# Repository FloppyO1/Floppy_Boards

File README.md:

# Floppy_Boards
Floppy Boards are a series of breakout boards for rapid prototyping which I developed as an alternative of Arduino.

These boards can provide good performance and many useful modules (such as: USB, I2C, SPI, timers etc.). I want to make several models, in order to have different boards for different applications.
For example, I am considering developing options for:

- Built-in battery monitoring & charging.   (to be done)
- Built-in DC motor control.                (to be done)
- Built-in servos & stepper-motor control.  (to be done)

# Why as an alternative to Arduino boards?
I am building this board because I was looking for a cheap, powerful and well supported development board in the marketplace, but I don’t find anything I like. On the other hand, I am learning a lot while making these Floppy Boards.
## Features
- Programmable with Arduino IDE and STMCubeIDE
- Planty of the module
- Small dimensions
- Lots of GPIO

### The most recent version I've made

The third version of the Floppy Board, this board has incorporated all possible improvements regarding the interface between the Floppy Board and the computer.
In this version, it excels over the others in the following aspects:

- The last upgrade includes a USB-C port, allowing you to power our projects and load firmware directly without the need for an ST-Link.
- Additionally, the board has been further downsized, featuring two holes on each side when inserted into a breadboard!
- I've added a pin where you can access the incoming 5V voltage from the USB , enabling you to power external circuits directly from the convenient USB-C.
- The silkscreen has been completely updated, making it much more legible and aesthetically pleasing.
- inally, we've introduced the option to install an EEPROM on the back of the board , enabling you to permanently save small amounts of data even in the absence of power.

## License

[CERN Open Hardware Licence Version 2 - Strongly Reciprocal](https://choosealicense.com/licenses/cern-ohl-s-2.0/#)

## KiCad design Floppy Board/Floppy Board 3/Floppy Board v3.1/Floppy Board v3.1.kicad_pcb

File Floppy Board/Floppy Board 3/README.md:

# Floppy Board rev:3.0/3.1

The third version of the Floppy Board, this board has incorporated all possible improvements regarding the interface between the Floppy Board and the computer.
In this version, it excels over the others in the following aspects:

- The last upgrade includes a USB-C port, allowing you to power our projects and load firmware directly without the need for an ST-Link.
- Additionally, the board has been further downsized, featuring two holes on each side when inserted into a breadboard!
- I've added a pin where you can access the incoming 5V voltage from the USB , enabling you to power external circuits directly from the convenient USB-C.
- The silkscreen has been completely updated, making it much more legible and aesthetically pleasing.
- inally, we've introduced the option to install an EEPROM on the back of the board , enabling you to permanently save small amounts of data even in the absence of power.

## License

[CERN Open Hardware Licence Version 2 - Strongly Reciprocal](https://choosealicense.com/licenses/cern-ohl-s-2.0/#)

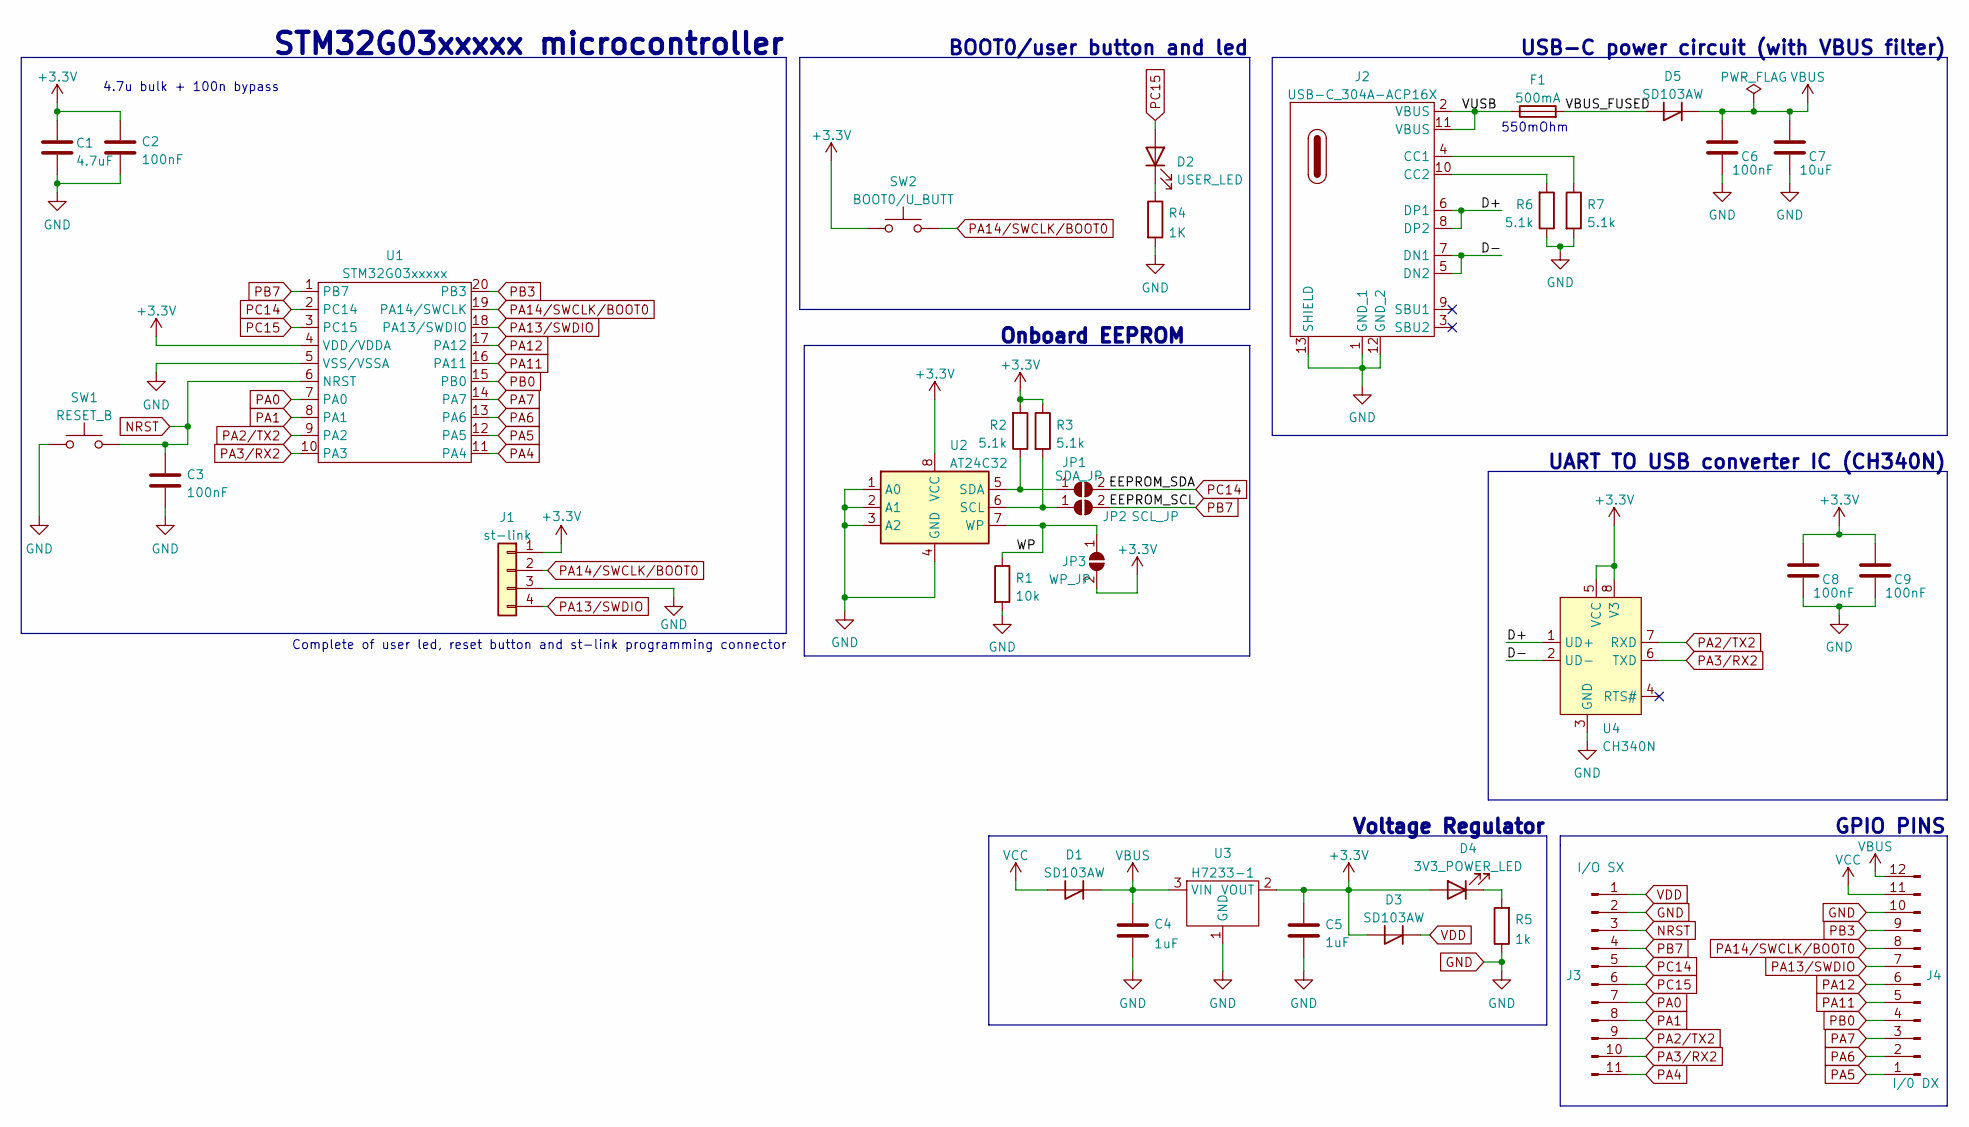
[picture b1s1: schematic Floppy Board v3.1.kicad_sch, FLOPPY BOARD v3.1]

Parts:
C1: 4.7uF; C_0805_2012Metric_Pad1.18x1.45mm_HandSolder
C2, C3, C6, C8, C9: 100nF; C_0805_2012Metric_Pad1.18x1.45mm_HandSolder
C4, C5: 1uF; C_0805_2012Metric_Pad1.18x1.45mm_HandSolder
C7: 10uF; C_0805_2012Metric_Pad1.18x1.45mm_HandSolder
D1, D5: SD103AW; D_SOD-123
D2: USER_LED; LED_0805_2012Metric_Pad1.15x1.40mm_HandSolder
D3: SD103AW; D_SOD-123F
D4: 3V3_POWER_LED; LED_0805_2012Metric_Pad1.15x1.40mm_HandSolder
F1: 500mA; Fuse_1206_3216Metric_Pad1.42x1.75mm_HandSolder
J1: st-link; PinHeader_1x04_P2.54mm_Vertical
J2: USB-C_304A-ACP16X; USB_C_304A-ACP16X
J3: I/O SX; PinHeader_1x11_P2.54mm_Vertical
J4: I/0 DX; PinHeader_1x12_P2.54mm_Vertical
JP1: SDA_JP; SolderJumper-2_P1.3mm_Open_RoundedPad1.0x1.5mm
JP2: SCL_JP; SolderJumper-2_P1.3mm_Open_RoundedPad1.0x1.5mm
JP3: WP_JP; SolderJumper-2_P1.3mm_Open_RoundedPad1.0x1.5mm
R1: 10k; R_0805_2012Metric_Pad1.20x1.40mm_HandSolder
R2, R3, R6, R7: 5.1k; R_0805_2012Metric_Pad1.20x1.40mm_HandSolder
R4: 1K; R_0805_2012Metric_Pad1.20x1.40mm_HandSolder
R5: 1k; R_0805_2012Metric_Pad1.20x1.40mm_HandSolder
SW1: RESET_B; SMD BUTTON 5.1x5.1
SW2: BOOT0/U_BUTT; SMD BUTTON 5.1x5.1
U1: STM32G03xxxxx; TSSOP-20_4.4x6.5mm_P0.65mm
U2: AT24C32; SOP-8_3.9x4.9mm_P1.27mm
U3: H7233-1; SOT-23
U4: CH340N; SOP-8_3.9x4.9mm_P1.27mm

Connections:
+3V3: C1.1, C2.1, C5.1, C8.1, C9.1, D3.2 (A), D4.2 (A), J1.1, JP3.2 (B), R2.2, R3.1, SW2.1, U1.4 (VDD/VDDA), U2.8 (VCC), U3.2 (VOUT), U4.5 (VCC), U4.8 (V3)
/D+: J2.6 (DP1), J2.8 (DP2), U4.1 (UD+)
/D-: J2.5 (DN2), J2.7 (DN1), U4.2 (UD-)
/VBUS_FUSED: D5.2 (A), F1.2
/VUSB: F1.1, J2.2 (VBUS), J2.11 (VBUS)
/WP: JP3.1 (A), R1.1, U2.7 (WP)
GND: C1.2, C2.2, C3.2, C4.2, C5.2, C6.2, C7.2, C8.2, C9.2, J1.3, J2.1 (GND_1), J2.12 (GND_2), J2.13 (SHIELD), J3.2, J4.10, R1.2, R4.2, R5.1, R6.1, R7.2, SW1.1, U1.5 (VSS/VSSA), U2.1 (A0), U2.2 (A1), U2.3 (A2), U2.4 (GND), U3.1 (GND), U4.3 (GND)
NRST: C3.1, J3.3, SW1.2, U1.6 (NRST)
unnamed: D2.1 (K), R4.1
unnamed: D4.1 (K), R5.2
unnamed: J2.4 (CC1), R7.1
unnamed: J2.10 (CC2), R6.2
unnamed: JP1.1 (A), R2.1, U2.5 (SDA)
unnamed: JP2.1 (A), R3.2, U2.6 (SCL)
PA0: J3.7, U1.7 (PA0)
PA1: J3.8, U1.8 (PA1)
PA2/TX2: J3.9, U1.9 (PA2), U4.7 (RXD)
PA3/RX2: J3.10, U1.10 (PA3), U4.6 (TXD)
PA4: J3.11, U1.11 (PA4)
PA5: J4.1, U1.12 (PA5)
PA6: J4.2, U1.13 (PA6)
PA7: J4.3, U1.14 (PA7)
PA11: J4.5, U1.16 (PA11)
PA12: J4.6, U1.17 (PA12)
PA13/SWDIO: J1.4, J4.7, U1.18 (PA13/SWDIO)
PA14/SWCLK/BOOT0: J1.2, J4.8, SW2.2, U1.19 (PA14/SWCLK)
PB0: J4.4, U1.15 (PB0)
PB3: J4.9, U1.20 (PB3)
PB7: J3.4, JP2.2 (B), U1.1 (PB7)
PC14: J3.5, JP1.2 (B), U1.2 (PC14)
PC15: D2.2 (A), J3.6, U1.3 (PC15)
VBUS: C4.1, C6.1, C7.1, D1.1 (K), D5.1 (K), J4.12, U3.3 (VIN)
VCC: D1.2 (A), J4.11
VDD: D3.1 (K), J3.1

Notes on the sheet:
USB-C power circuit (with VBUS filter)
4.7u bulk + 100n bypass
Voltage Regulator
STM32G03xxxxx microcontroller
550mOhm
GPIO PINS
UART TO USB converter IC (CH340N)
BOOT0/user button and led
Complete of user led, reset button and st-link programming connector
Onboard EEPROM

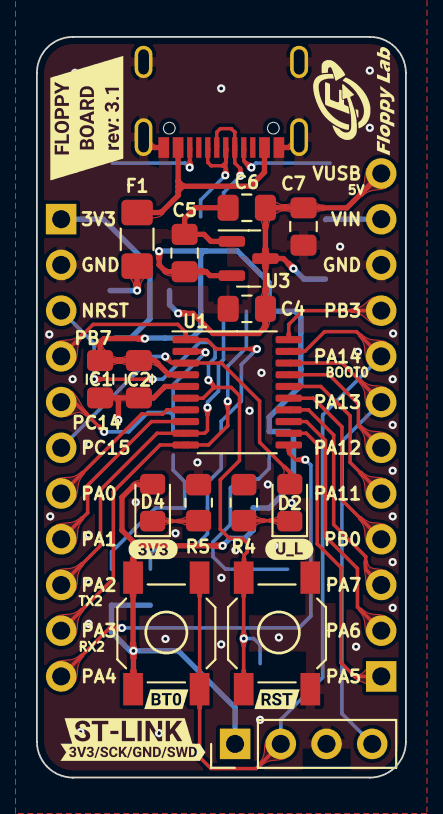
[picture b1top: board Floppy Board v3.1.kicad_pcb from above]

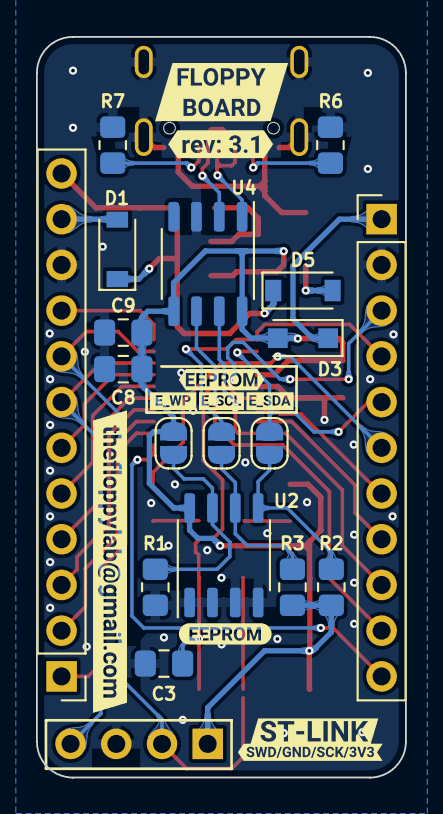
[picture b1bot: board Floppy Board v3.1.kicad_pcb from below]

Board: 2 copper layers, 20.5 x 41.1 mm, 52 parts (28 on the bottom side), 34 nets.

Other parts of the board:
kibuzzard-644D5A83: G***; kibuzzard-644D5A83
kibuzzard-644D5AD1: G***; kibuzzard-644D5AD1
kibuzzard-644D5AFD: G***; kibuzzard-644D5AFD
kibuzzard-644D5B14: G***; kibuzzard-644D5B14
kibuzzard-644D5C5F: G***; kibuzzard-644D5C5F
kibuzzard-644D5C68: G***; kibuzzard-644D5C68
kibuzzard-644D5C93: G***; kibuzzard-644D5C93
kibuzzard-644D5CBA: G***; kibuzzard-644D5CBA
kibuzzard-644D5F43: G***; kibuzzard-644D5F43
kibuzzard-644D56F9: G***; kibuzzard-644D56F9
kibuzzard-644D58F1: G***; kibuzzard-644D58F1
kibuzzard-644D571B: G***; kibuzzard-644D571B
kibuzzard-644D5750: G***; kibuzzard-644D5750
kibuzzard-644D5758: G***; kibuzzard-644D5758
kibuzzard-644D5814: G***; kibuzzard-644D5814
kibuzzard-644D5953: G***; kibuzzard-644D5953
kibuzzard-644D6722: G***; kibuzzard-644D6722

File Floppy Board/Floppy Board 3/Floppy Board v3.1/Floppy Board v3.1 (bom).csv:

"Reference","Value","Footprint","Qtà"
"C1","4.7uF","Capacitor_SMD:C_0805_2012Metric_Pad1.18x1.45mm_HandSolder","1"
"C2, C3, C6, C8, C9","100nF","Capacitor_SMD:C_0805_2012Metric_Pad1.18x1.45mm_HandSolder","5"
"C4, C5","1uF","Capacitor_SMD:C_0805_2012Metric_Pad1.18x1.45mm_HandSolder","2"
"C7","10uF","Capacitor_SMD:C_0805_2012Metric_Pad1.18x1.45mm_HandSolder","1"
"D1, D5","SD103AW","Diode_SMD:D_SOD-123","2"
"D2","USER_LED","LED_SMD:LED_0805_2012Metric_Pad1.15x1.40mm_HandSolder","1"
"D3","SD103AW","Diode_SMD:D_SOD-123F","1"
"D4","3V3_POWER_LED","LED_SMD:LED_0805_2012Metric_Pad1.15x1.40mm_HandSolder","1"
"F1","500mA","Fuse:Fuse_1206_3216Metric_Pad1.42x1.75mm_HandSolder","1"
"J1","st-link","Connector_PinHeader_2.54mm:PinHeader_1x04_P2.54mm_Vertical","1"
"J2","USB-C_304A-ACP16X","_MIA footprint:USB_C_304A-ACP16X","1"
"J3","I/O SX","Connector_PinHeader_2.54mm:PinHeader_1x11_P2.54mm_Vertical","1"
"J4","I/0 DX","Connector_PinHeader_2.54mm:PinHeader_1x12_P2.54mm_Vertical","1"
"JP1","SDA_JP","Jumper:SolderJumper-2_P1.3mm_Open_RoundedPad1.0x1.5mm","1"
"JP2","SCL_JP","Jumper:SolderJumper-2_P1.3mm_Open_RoundedPad1.0x1.5mm","1"
"JP3","WP_JP","Jumper:SolderJumper-2_P1.3mm_Open_RoundedPad1.0x1.5mm","1"
"R1","10k","Resistor_SMD:R_0805_2012Metric_Pad1.20x1.40mm_HandSolder","1"
"R2, R3, R6, R7","5.1k","Resistor_SMD:R_0805_2012Metric_Pad1.20x1.40mm_HandSolder","4"
"R4","1K","Resistor_SMD:R_0805_2012Metric_Pad1.20x1.40mm_HandSolder","1"
"R5","1k","Resistor_SMD:R_0805_2012Metric_Pad1.20x1.40mm_HandSolder","1"
"SW1","RESET_B","_MIA footprint:SMD BUTTON 5.1x5.1","1"
"SW2","BOOT0/U_BUTT","_MIA footprint:SMD BUTTON 5.1x5.1","1"
"U1","STM32G03xxxxx","Package_SO:TSSOP-20_4.4x6.5mm_P0.65mm","1"
"U2","AT24C32","Package_SO:SOP-8_3.9x4.9mm_P1.27mm","1"
"U3","H7233-1","Package_TO_SOT_SMD:SOT-23","1"
"U4","CH340N","Package_SO:SOP-8_3.9x4.9mm_P1.27mm","1"

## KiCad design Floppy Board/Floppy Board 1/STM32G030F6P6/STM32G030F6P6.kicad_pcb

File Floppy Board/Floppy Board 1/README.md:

# Floppy Board rev:1.0

This is the first prototype of the Floppy Board.

## License

[CERN Open Hardware Licence Version 2 - Strongly Reciprocal](https://choosealicense.com/licenses/cern-ohl-s-2.0/#)

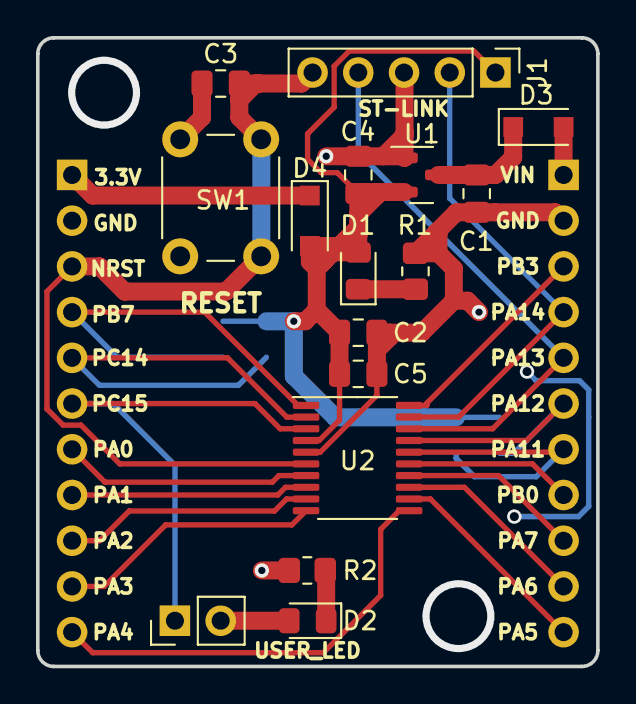
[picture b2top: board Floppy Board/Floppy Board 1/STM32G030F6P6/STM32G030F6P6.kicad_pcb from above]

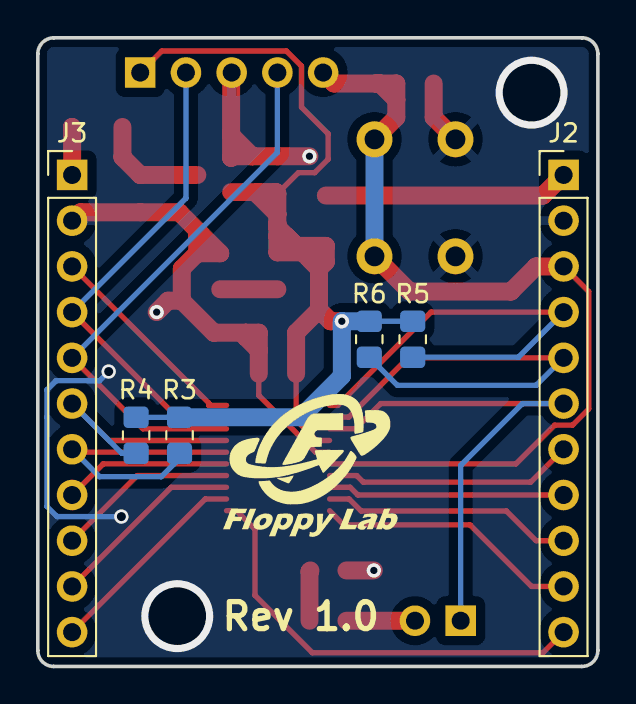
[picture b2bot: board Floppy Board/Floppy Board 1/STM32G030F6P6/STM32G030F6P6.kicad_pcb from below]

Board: 2 copper layers, 31.1 x 34.9 mm, 22 parts (6 on the bottom side), 26 nets.

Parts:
C1, C4: 1u; C_0805_2012Metric_Pad1.18x1.45mm_HandSolder
C2: 4.7u; C_0805_2012Metric_Pad1.18x1.45mm_HandSolder
C3: 0.1U; C_0805_2012Metric_Pad1.18x1.45mm_HandSolder
C5: 100n; C_0805_2012Metric_Pad1.18x1.45mm_HandSolder
D1: POWER_LED; LED_0805_2012Metric_Pad1.15x1.40mm_HandSolder
D2: USER_LED; LED_0805_2012Metric_Pad1.15x1.40mm_HandSolder
D3, D4: 1N4002; D_SOD-123F
J1: stlink; PinHeader_1x05_P2.54mm_Vertical
J2: I/O SX; PinHeader_1x11_P2.54mm_Vertical
J3: I/0 DX; PinHeader_1x11_P2.54mm_Vertical
JP1: UL JUMP.; PinHeader_1x02_P2.54mm_Vertical
R1: 1k; R_0805_2012Metric_Pad1.20x1.40mm_HandSolder
R2: 1K; R_0805_2012Metric_Pad1.20x1.40mm_HandSolder
R3, R4, R5, R6: 4.7k; R_0805_2012Metric_Pad1.20x1.40mm_HandSolder
SW1: RESET_BUTTON; SW_PUSH_6mm
U1: H7233-1; SOT-23
U2: STM32G030F6P6; TSSOP-20_4.4x6.5mm_P0.65mm

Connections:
+3V3: C2.1, C4.1, C5.1, D1.2 (A), D4.2 (A), J1.1, R3.1, R4.1, R5.1, R6.1, U1.2 (VOUT), U2.4 (VDD/VDDA)
GND: C1.2, C2.2, C3.2, C4.2, C5.2, J1.3, J2.2, J3.2, R1.1, R2.2, SW1.1, U1.1 (GND), U2.5 (VSS/VSSA)
NRST: C3.1, J1.5, J2.3, SW1.2, U2.6 (NRST)
unnamed: C1.1, D3.1 (K), U1.3 (VIN)
unnamed: D1.1 (K), R1.2
unnamed: D2.1 (K), R2.1
unnamed: D2.2 (A), JP1.2 (B)
PA0: J2.7, U2.7 (PA0)
PA1: J2.8, U2.8 (PA1)
PA2: J2.9, U2.9 (PA2)
PA3: J2.10, U2.10 (PA3)
PA4: J2.11, U2.11 (PA4)
PA5: J3.11, U2.12 (PA5)
PA6: J3.10, U2.13 (PA6)
PA7: J3.9, U2.14 (PA7)
PA11: J3.7, R3.2, U2.16 (PA11)
PA12: J3.6, R4.2, U2.17 (PA12)
PA13/SWDIO: J1.4, J3.5, U2.18 (PA13/SWDIO)
PA14/SWCLK: J1.2, J3.4, U2.19 (PA14/SWCLK)
PB0: J3.8, U2.15 (PB0)
PB3: J3.3, U2.20 (PB3)
PB7: J2.4, R5.2, U2.1 (PB7)
PC14: J2.5, R6.2, U2.2 (PC14)
PC15: J2.6, JP1.1 (A), U2.3 (PC15)
VDD: D4.1 (K), J2.1
VIN: D3.2 (A), J3.1

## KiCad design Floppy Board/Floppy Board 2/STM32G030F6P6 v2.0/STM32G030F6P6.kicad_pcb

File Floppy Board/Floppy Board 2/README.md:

# Floppy Board rev:2.0

This is the second version of the Floppy Board, and it includes a few small improvements that make it simpler and faster to use.
The improvements that I made are as follows:

- The total width has been reduced, allowing this version to be used with only one breadboard.
- The 3.3V output pin now has precisely 3.3V (3.263V), ensuring no more 3V output!
- Pin names have been added on each side of the board.
- The board now has a slimmer profile that makes it possible to use it upside down.
- The microcontroller is the same as the first Floppy Board, but it can be upgraded with an equivalent MCU that has double the FLASH memory. The more capable MCU is the STM32G031F8P6, which has 32kB more memory than the old one (so 64kB in total). These boards are compatible with Arduino IDE, meaning they can be easily programmed by users who are less experienced.

## License

[CERN Open Hardware Licence Version 2 - Strongly Reciprocal](https://choosealicense.com/licenses/cern-ohl-s-2.0/#)

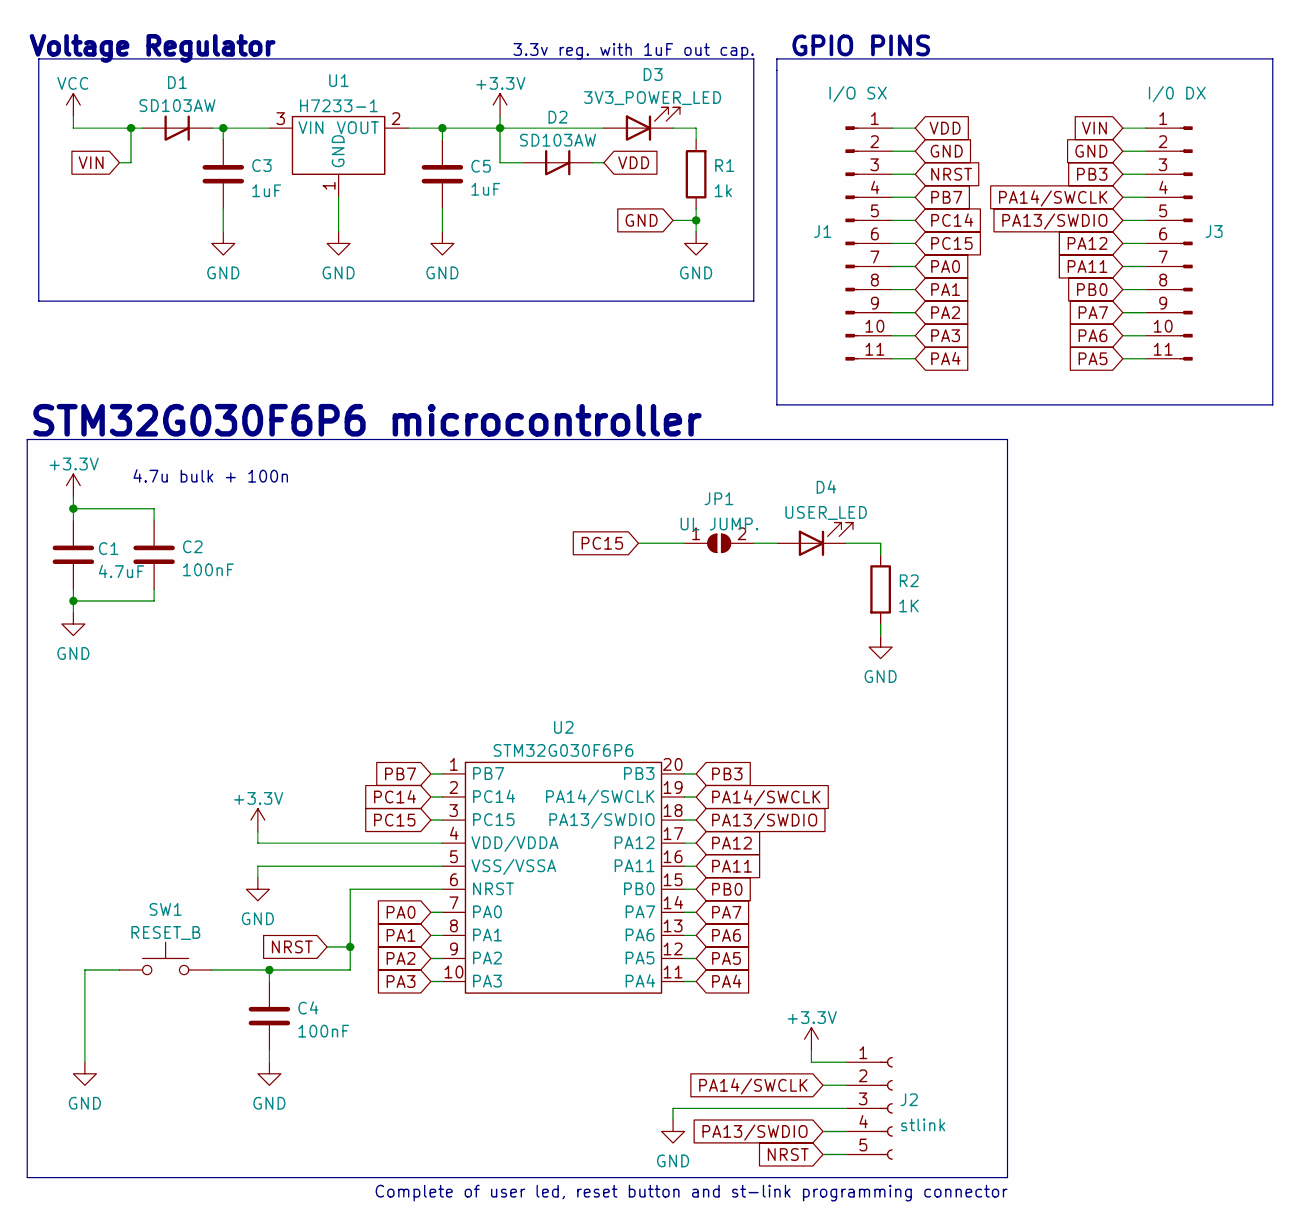
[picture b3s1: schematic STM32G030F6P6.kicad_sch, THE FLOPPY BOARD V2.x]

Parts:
C1: 4.7uF; C_0805_2012Metric_Pad1.18x1.45mm_HandSolder
C2, C4: 100nF; C_0805_2012Metric_Pad1.18x1.45mm_HandSolder
C3, C5: 1uF; C_0805_2012Metric_Pad1.18x1.45mm_HandSolder
D1: SD103AW; D_SOD-123
D2: SD103AW; D_SOD-123F
D3: 3V3_POWER_LED; LED_0805_2012Metric_Pad1.15x1.40mm_HandSolder
D4: USER_LED; LED_0805_2012Metric_Pad1.15x1.40mm_HandSolder
J1: I/O SX; PinHeader_1x11_P2.54mm_Vertical
J2: stlink; PinHeader_1x05_P2.54mm_Vertical
J3: I/0 DX; PinHeader_1x11_P2.54mm_Vertical
JP1: UL JUMP.; SolderJumper-2_P1.3mm_Open_RoundedPad1.0x1.5mm
R1: 1k; R_0805_2012Metric_Pad1.20x1.40mm_HandSolder
R2: 1K; R_0805_2012Metric_Pad1.20x1.40mm_HandSolder
SW1: RESET_B; SMD BUTTON 5.1x5.1
U1: H7233-1; SOT-23
U2: STM32G030F6P6; TSSOP-20_4.4x6.5mm_P0.65mm

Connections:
+3V3: C1.1, C2.1, C5.1, D2.2 (A), D3.2 (A), J2.1, U1.2 (VOUT), U2.4 (VDD/VDDA)
GND: C1.2, C2.2, C3.2, C4.2, C5.2, J1.2, J2.3, J3.2, R1.1, R2.2, SW1.1, U1.1 (GND), U2.5 (VSS/VSSA)
NRST: C4.1, J1.3, J2.5, SW1.2, U2.6 (NRST)
unnamed: C3.1, D1.1 (K), U1.3 (VIN)
unnamed: D3.1 (K), R1.2
unnamed: D4.1 (K), R2.1
unnamed: D4.2 (A), JP1.2 (B)
PA0: J1.7, U2.7 (PA0)
PA1: J1.8, U2.8 (PA1)
PA2: J1.9, U2.9 (PA2)
PA3: J1.10, U2.10 (PA3)
PA4: J1.11, U2.11 (PA4)
PA5: J3.11, U2.12 (PA5)
PA6: J3.10, U2.13 (PA6)
PA7: J3.9, U2.14 (PA7)
PA11: J3.7, U2.16 (PA11)
PA12: J3.6, U2.17 (PA12)
PA13/SWDIO: J2.4, J3.5, U2.18 (PA13/SWDIO)
PA14/SWCLK: J2.2, J3.4, U2.19 (PA14/SWCLK)
PB0: J3.8, U2.15 (PB0)
PB3: J3.3, U2.20 (PB3)
PB7: J1.4, U2.1 (PB7)
PC14: J1.5, U2.2 (PC14)
PC15: J1.6, JP1.1 (A), U2.3 (PC15)
VDD: D2.1 (K), J1.1
VIN: D1.2 (A), J3.1

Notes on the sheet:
3.3v reg. with 1uF out cap.
GPIO PINS
4.7u bulk + 100n
Complete of user led, reset button and st-link programming connector
STM32G030F6P6 microcontroller
Voltage Regulator

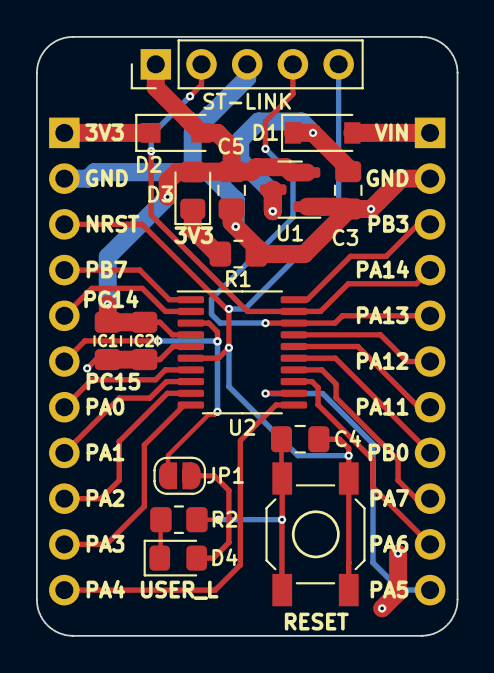
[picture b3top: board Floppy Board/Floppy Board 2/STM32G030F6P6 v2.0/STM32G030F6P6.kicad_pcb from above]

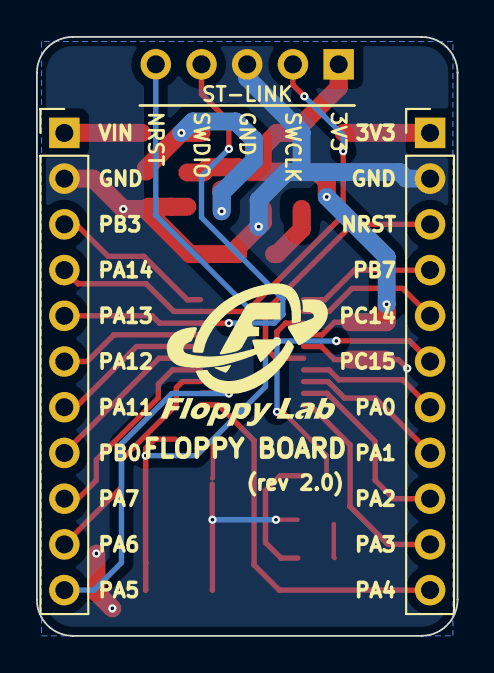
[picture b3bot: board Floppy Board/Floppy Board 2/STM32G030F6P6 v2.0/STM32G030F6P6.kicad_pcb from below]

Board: 2 copper layers, 23.4 x 33.3 mm, 18 parts (2 on the bottom side), 26 nets.

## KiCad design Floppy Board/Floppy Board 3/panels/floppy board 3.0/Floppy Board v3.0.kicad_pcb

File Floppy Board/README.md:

# Floppy Board

Inside this folder there are all the files of the base version of the Floppy Board.

There are 3 major versions:
- v1.0, that is the first prototype that I've made.
- v2.0, which is the second attempt, is an improved version of 1.0, it is good because it is the smallest of the three versions.
- v3.x, which is the last version that includes the connections between the Floppy Board and the computer.

## License

[CERN Open Hardware Licence Version 2 - Strongly Reciprocal](https://choosealicense.com/licenses/cern-ohl-s-2.0/#)

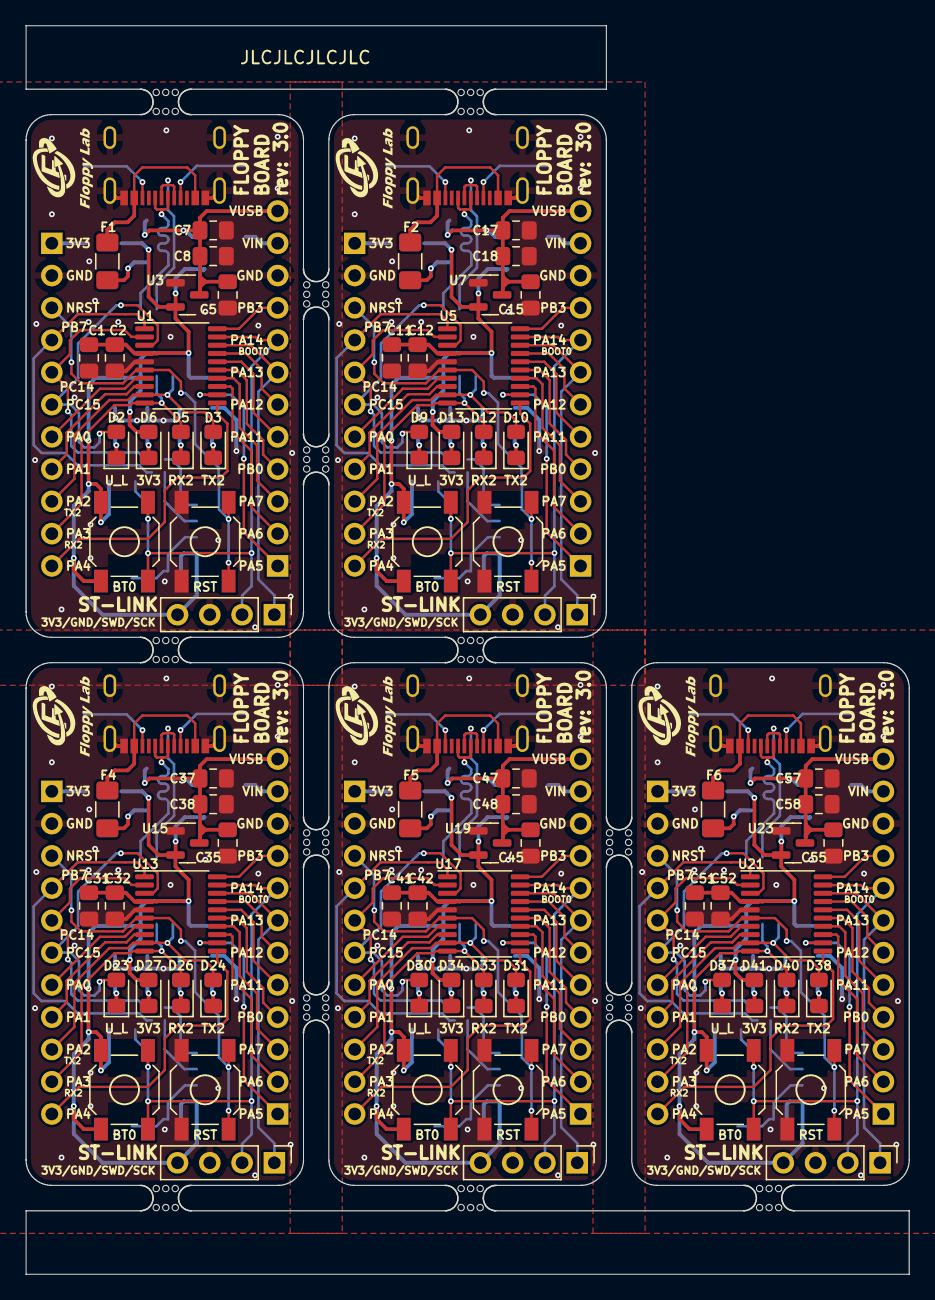
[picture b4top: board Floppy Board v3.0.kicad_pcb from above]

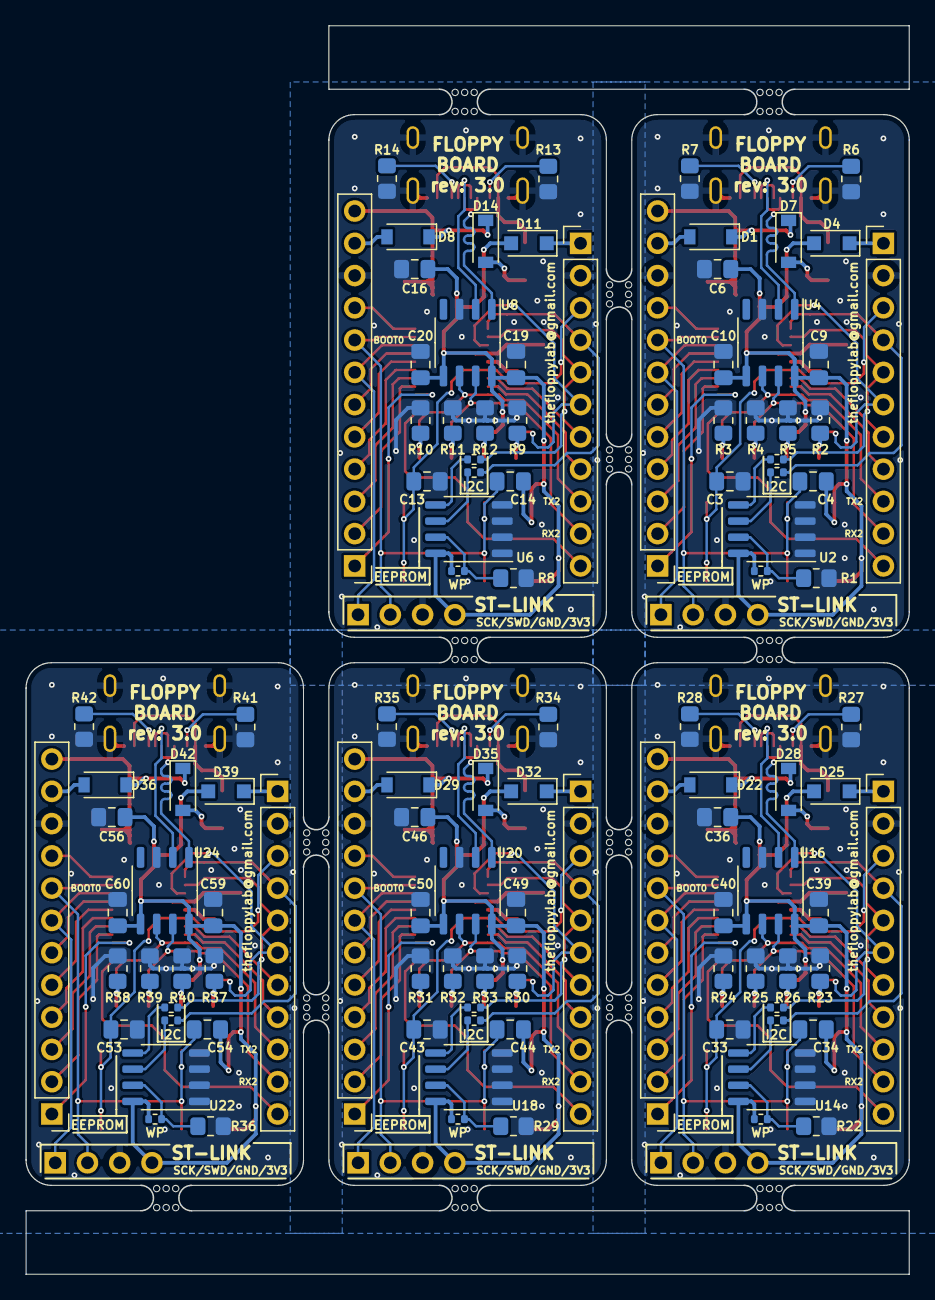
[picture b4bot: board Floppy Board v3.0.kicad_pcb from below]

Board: 2 copper layers, 69.5 x 98.3 mm, 203 parts (110 on the bottom side), 36 nets.

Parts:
C1, C11, C31, C41, C51: 4.7uF; C_0805_2012Metric_Pad1.18x1.45mm_HandSolder
C2, C3, C4, C7, C9, C10, C12, C13, C14, C17, C19, C20, C32, C33, C34, C37, C39, C40, C42, C43, C44, C47, C49, C50, C52, C53, C54, C57, C59, C60: 100nF; C_0805_2012Metric_Pad1.18x1.45mm_HandSolder
C5, C6, C15, C16, C35, C36, C45, C46, C55, C56: 1uF; C_0805_2012Metric_Pad1.18x1.45mm_HandSolder
C8, C18, C38, C48, C58: 10uF; C_0805_2012Metric_Pad1.18x1.45mm_HandSolder
D1, D7, D8, D14, D22, D28, D29, D35, D36, D42: SD103AW; D_SOD-123
D2, D9, D23, D30, D37: USER_LED; LED_0805_2012Metric_Pad1.15x1.40mm_HandSolder
D3, D10, D24, D31, D38: TX2; LED_0805_2012Metric_Pad1.15x1.40mm_HandSolder
D4, D11, D25, D32, D39: SD103AW; D_SOD-123F
D5, D12, D26, D33, D40: RX2; LED_0805_2012Metric_Pad1.15x1.40mm_HandSolder
D6, D13, D27, D34, D41: 3V3_POWER_LED; LED_0805_2012Metric_Pad1.15x1.40mm_HandSolder
F1, F2, F4, F5, F6: 500mA; Fuse_1206_3216Metric_Pad1.42x1.75mm_HandSolder
J1, J5, J13, J17, J21: st-link; PinHeader_1x04_P2.54mm_Vertical
J2, J6, J14, J18, J22: USB-C_304A-ACP16X; USB_C_304A-ACP16X
J3, J7, J15, J19, J23: I/O SX; PinHeader_1x11_P2.54mm_Vertical
J4, J8, J16, J20, J24: I/0 DX; PinHeader_1x12_P2.54mm_Vertical
JP1, JP4, JP10, JP13, JP16: SDA_JP; R_0402_1005Metric
JP2, JP5, JP11, JP14, JP17: SCL_JP; R_0402_1005Metric
JP3, JP6, JP12, JP15, JP18: WP_JP; R_0402_1005Metric
R1, R8, R22, R29, R36: 10k; R_0805_2012Metric_Pad1.20x1.40mm_HandSolder
R2, R3, R4, R9, R10, R11, R23, R24, R25, R30, R31, R32, R37, R38, R39: 1K; R_0805_2012Metric_Pad1.20x1.40mm_HandSolder
R5, R12, R26, R33, R40: 1k; R_0805_2012Metric_Pad1.20x1.40mm_HandSolder
R6, R7, R13, R14, R27, R28, R34, R35, R41, R42: 5.1k; R_0805_2012Metric_Pad1.20x1.40mm_HandSolder
SW1, SW3, SW7, SW9, SW11: RESET_B; SMD BUTTON 5.1x5.1
SW2, SW4, SW8, SW10, SW12: BOOT0/U_BUTT; SMD BUTTON 5.1x5.1
U1, U5, U13, U17, U21: STM32G03xxxxx; TSSOP-20_4.4x6.5mm_P0.65mm
U2, U6, U14, U18, U22: AT24C32; SOP-8_3.9x4.9mm_P1.27mm
U3, U7, U15, U19, U23: H7233-1; SOT-23
U4, U8, U16, U20, U24: CH340N; SOP-8_3.9x4.9mm_P1.27mm
mouse-bite-2mm-slot, mouse-bite-2mm-slot#2, mouse-bite-2mm-slot#3, mouse-bite-2mm-slot#4, mouse-bite-2mm-slot#5, mouse-bite-2mm-slot#6, mouse-bite-2mm-slot#7, mouse-bite-2mm-slot#8, mouse-bite-2mm-slot#9, mouse-bite-2mm-slot#10, mouse-bite-2mm-slot#11, mouse-bite-2mm-slot#12, mouse-bite-2mm-slot#13: VAL**; mouse-bite-2mm-slot

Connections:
+3V3: C1.1, C2.1, C4.2, C6.1, C9.1, C10.1, C11.1, C12.1, C14.2, C16.1, C19.1, C20.1, C31.1, C32.1, C34.2, C36.1, C39.1, C40.1, C41.1, C42.1, C44.2, C46.1, C49.1, C50.1, C51.1, C52.1, C54.2, C56.1, C59.1, C60.1, D4.2 (A), D6.2 (A), D11.2 (A), D13.2 (A), D25.2 (A), D27.2 (A), D32.2 (A), D34.2 (A), D39.2 (A), D41.2 (A), J1.4, J5.4, J13.4, J17.4, J21.4, JP3.2 (B), JP6.2 (B), JP12.2 (B), JP15.2 (B), JP18.2 (B), SW2.1, SW4.1, SW8.1, SW10.1, SW12.1, U1.4 (VDD/VDDA), U2.8 (VCC), U3.2 (VOUT), U4.5 (VCC), U4.8 (V3), U5.4 (VDD/VDDA), U6.8 (VCC), U7.2 (VOUT), U8.5 (VCC), U8.8 (V3), U13.4 (VDD/VDDA), U14.8 (VCC), U15.2 (VOUT), U16.5 (VCC), U16.8 (V3), U17.4 (VDD/VDDA), U18.8 (VCC), U19.2 (VOUT), U20.5 (VCC), U20.8 (V3), U21.4 (VDD/VDDA), U22.8 (VCC), U23.2 (VOUT), U24.5 (VCC), U24.8 (V3)
/D+: J2.6 (DP1), J2.8 (DP2), J6.6 (DP1), J6.8 (DP2), J14.6 (DP1), J14.8 (DP2), J18.6 (DP1), J18.8 (DP2), J22.6 (DP1), J22.8 (DP2), U4.1 (UD+), U8.1 (UD+), U16.1 (UD+), U20.1 (UD+), U24.1 (UD+)
/D-: J2.5 (DN2), J2.7 (DN1), J6.5 (DN2), J6.7 (DN1), J14.5 (DN2), J14.7 (DN1), J18.5 (DN2), J18.7 (DN1), J22.5 (DN2), J22.7 (DN1), U4.2 (UD-), U8.2 (UD-), U16.2 (UD-), U20.2 (UD-), U24.2 (UD-)
/VUSB: F1.1, F2.1, F4.1, F5.1, F6.1, J2.2 (VBUS), J2.11 (VBUS), J6.2 (VBUS), J6.11 (VBUS), J14.2 (VBUS), J14.11 (VBUS), J18.2 (VBUS), J18.11 (VBUS), J22.2 (VBUS), J22.11 (VBUS)
GND: C1.2, C2.2, C3.2, C5.2, C6.2, C7.2, C8.2, C9.2, C10.2, C11.2, C12.2, C13.2, C15.2, C16.2, C17.2, C18.2, C19.2, C20.2, C31.2, C32.2, C33.2, C35.2, C36.2, C37.2, C38.2, C39.2, C40.2, C41.2, C42.2, C43.2, C45.2, C46.2, C47.2, C48.2, C49.2, C50.2, C51.2, C52.2, C53.2, C55.2, C56.2, C57.2, C58.2, C59.2, C60.2, J1.3, J2.1 (GND_1), J2.12 (GND_2), J2.13 (SHIELD), J3.2, J4.10, J5.3, J6.1 (GND_1), J6.12 (GND_2), J6.13 (SHIELD), J7.2, J8.10, J13.3, J14.1 (GND_1), J14.12 (GND_2), J14.13 (SHIELD), J15.2, J16.10, J17.3, J18.1 (GND_1), J18.12 (GND_2), J18.13 (SHIELD), J19.2, J20.10, J21.3, J22.1 (GND_1), J22.12 (GND_2), J22.13 (SHIELD), J23.2, J24.10, R1.2, R2.2, R3.2, R4.2, R5.1, R6.1, R7.2, R8.2, R9.2, R10.2, R11.2, R12.1, R13.1, R14.2, R22.2, R23.2, R24.2, R25.2, R26.1, R27.1, R28.2, R29.2, R30.2, R31.2, R32.2, R33.1, R34.1, R35.2, R36.2, R37.2, R38.2, R39.2, R40.1, R41.1, R42.2, SW1.1, SW3.1, SW7.1, SW9.1, SW11.1, U1.5 (VSS/VSSA), U2.1 (A0), U2.2 (A1), U2.3 (A2), U2.4 (GND), U3.1 (GND), U4.3 (GND), U5.5 (VSS/VSSA), U6.1 (A0), U6.2 (A1), U6.3 (A2), U6.4 (GND), U7.1 (GND), U8.3 (GND), U13.5 (VSS/VSSA), U14.1 (A0), U14.2 (A1), U14.3 (A2), U14.4 (GND), U15.1 (GND), U16.3 (GND), U17.5 (VSS/VSSA), U18.1 (A0), U18.2 (A1), U18.3 (A2), U18.4 (GND), U19.1 (GND), U20.3 (GND), U21.5 (VSS/VSSA), U22.1 (A0), U22.2 (A1), U22.3 (A2), U22.4 (GND), U23.1 (GND), U24.3 (GND)
NRST: C3.1, C13.1, C33.1, C43.1, C53.1, J3.3, J7.3, J15.3, J19.3, J23.3, SW1.2, SW3.2, SW7.2, SW9.2, SW11.2, U1.6 (NRST), U5.6 (NRST), U13.6 (NRST), U17.6 (NRST), U21.6 (NRST)
unnamed: D2.1 (K), D9.1 (K), D23.1 (K), D30.1 (K), D37.1 (K), R2.1, R9.1, R23.1, R30.1, R37.1
unnamed: D3.1 (K), D10.1 (K), D24.1 (K), D31.1 (K), D38.1 (K), R3.1, R10.1, R24.1, R31.1, R38.1
unnamed: D5.1 (K), D12.1 (K), D26.1 (K), D33.1 (K), D40.1 (K), R4.1, R11.1, R25.1, R32.1, R39.1
unnamed: D6.1 (K), D13.1 (K), D27.1 (K), D34.1 (K), D41.1 (K), R5.2, R12.2, R26.2, R33.2, R40.2
unnamed: D7.2 (A), D14.2 (A), D28.2 (A), D35.2 (A), D42.2 (A), F1.2, F2.2, F4.2, F5.2, F6.2
unnamed: J2.4 (CC1), J6.4 (CC1), J14.4 (CC1), J18.4 (CC1), J22.4 (CC1), R7.1, R14.1, R28.1, R35.1, R42.1
unnamed: J2.10 (CC2), J6.10 (CC2), J14.10 (CC2), J18.10 (CC2), J22.10 (CC2), R6.2, R13.2, R27.2, R34.2, R41.2
unnamed: JP1.1 (A), JP4.1 (A), JP10.1 (A), JP13.1 (A), JP16.1 (A), U2.5 (SDA), U6.5 (SDA), U14.5 (SDA), U18.5 (SDA), U22.5 (SDA)
unnamed: JP2.1 (A), JP5.1 (A), JP11.1 (A), JP14.1 (A), JP17.1 (A), U2.6 (SCL), U6.6 (SCL), U14.6 (SCL), U18.6 (SCL), U22.6 (SCL)
unnamed: JP3.1 (A), JP6.1 (A), JP12.1 (A), JP15.1 (A), JP18.1 (A), R1.1, R8.1, R22.1, R29.1, R36.1, U2.7 (WP), U6.7 (WP), U14.7 (WP), U18.7 (WP), U22.7 (WP)
PA0: J3.7, J7.7, J15.7, J19.7, J23.7, U1.7 (PA0), U5.7 (PA0), U13.7 (PA0), U17.7 (PA0), U21.7 (PA0)
PA1: J3.8, J7.8, J15.8, J19.8, J23.8, U1.8 (PA1), U5.8 (PA1), U13.8 (PA1), U17.8 (PA1), U21.8 (PA1)
PA2/TX2: D3.2 (A), D10.2 (A), D24.2 (A), D31.2 (A), D38.2 (A), J3.9, J7.9, J15.9, J19.9, J23.9, U1.9 (PA2), U4.6 (TXD), U5.9 (PA2), U8.6 (TXD), U13.9 (PA2), U16.6 (TXD), U17.9 (PA2), U20.6 (TXD), U21.9 (PA2), U24.6 (TXD)
PA3/RX2: D5.2 (A), D12.2 (A), D26.2 (A), D33.2 (A), D40.2 (A), J3.10, J7.10, J15.10, J19.10, J23.10, U1.10 (PA3), U4.7 (RXD), U5.10 (PA3), U8.7 (RXD), U13.10 (PA3), U16.7 (RXD), U17.10 (PA3), U20.7 (RXD), U21.10 (PA3), U24.7 (RXD)
PA4: J3.11, J7.11, J15.11, J19.11, J23.11, U1.11 (PA4), U5.11 (PA4), U13.11 (PA4), U17.11 (PA4), U21.11 (PA4)
PA5: J4.1, J8.1, J16.1, J20.1, J24.1, U1.12 (PA5), U5.12 (PA5), U13.12 (PA5), U17.12 (PA5), U21.12 (PA5)
PA6: J4.2, J8.2, J16.2, J20.2, J24.2, U1.13 (PA6), U5.13 (PA6), U13.13 (PA6), U17.13 (PA6), U21.13 (PA6)
PA7: J4.3, J8.3, J16.3, J20.3, J24.3, U1.14 (PA7), U5.14 (PA7), U13.14 (PA7), U17.14 (PA7), U21.14 (PA7)
PA11: J4.5, J8.5, J16.5, J20.5, J24.5, U1.16 (PA11), U5.16 (PA11), U13.16 (PA11), U17.16 (PA11), U21.16 (PA11)
PA12: J4.6, J8.6, J16.6, J20.6, J24.6, U1.17 (PA12), U5.17 (PA12), U13.17 (PA12), U17.17 (PA12), U21.17 (PA12)
PA13/SWDIO: J1.1, J4.7, J5.1, J8.7, J13.1, J16.7, J17.1, J20.7, J21.1, J24.7, U1.18 (PA13/SWDIO), U5.18 (PA13/SWDIO), U13.18 (PA13/SWDIO), U17.18 (PA13/SWDIO), U21.18 (PA13/SWDIO)
PA14/SWCLK/BOOT0: C4.1, C14.1, C34.1, C44.1, C54.1, J1.2, J4.8, J5.2, J8.8, J13.2, J16.8, J17.2, J20.8, J21.2, J24.8, SW2.2, SW4.2, SW8.2, SW10.2, SW12.2, U1.19 (PA14/SWCLK), U5.19 (PA14/SWCLK), U13.19 (PA14/SWCLK), U17.19 (PA14/SWCLK), U21.19 (PA14/SWCLK)
PB0: J4.4, J8.4, J16.4, J20.4, J24.4, U1.15 (PB0), U5.15 (PB0), U13.15 (PB0), U17.15 (PB0), U21.15 (PB0)
PB3: J4.9, J8.9, J16.9, J20.9, J24.9, U1.20 (PB3), U5.20 (PB3), U13.20 (PB3), U17.20 (PB3), U21.20 (PB3)
PB7: J3.4, J7.4, J15.4, J19.4, J23.4, JP2.2 (B), JP5.2 (B), JP11.2 (B), JP14.2 (B), JP17.2 (B), U1.1 (PB7), U5.1 (PB7), U13.1 (PB7), U17.1 (PB7), U21.1 (PB7)
PC14: J3.5, J7.5, J15.5, J19.5, J23.5, JP1.2 (B), JP4.2 (B), JP10.2 (B), JP13.2 (B), JP16.2 (B), U1.2 (PC14), U5.2 (PC14), U13.2 (PC14), U17.2 (PC14), U21.2 (PC14)
PC15: D2.2 (A), D9.2 (A), D23.2 (A), D30.2 (A), D37.2 (A), J3.6, J7.6, J15.6, J19.6, J23.6, U1.3 (PC15), U5.3 (PC15), U13.3 (PC15), U17.3 (PC15), U21.3 (PC15)
VBUS: C5.1, C7.1, C8.1, C15.1, C17.1, C18.1, C35.1, C37.1, C38.1, C45.1, C47.1, C48.1, C55.1, C57.1, C58.1, D1.1 (K), D7.1 (K), D8.1 (K), D14.1 (K), D22.1 (K), D28.1 (K), D29.1 (K), D35.1 (K), D36.1 (K), D42.1 (K), J4.12, J8.12, J16.12, J20.12, J24.12, U3.3 (VIN), U7.3 (VIN), U15.3 (VIN), U19.3 (VIN), U23.3 (VIN)
VCC: D1.2 (A), D8.2 (A), D22.2 (A), D29.2 (A), D36.2 (A), J4.11, J8.11, J16.11, J20.11, J24.11
VDD: D4.1 (K), D11.1 (K), D25.1 (K), D32.1 (K), D39.1 (K), J3.1, J7.1, J15.1, J19.1, J23.1

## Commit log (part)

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2023-09-17 Create LICENSE
2023-09-17 Update LICENSE cern permessive
2023-09-17 Update LICENSE
2023-09-17 added all the files
2023-09-17 logo update
2023-09-17 footprint and simbol FB3
2023-09-17 pinout folder and files
2023-10-17 added pinout template folder
2023-12-03 updated pinout FB3.1
2024-05-15 updated pinout
2025-02-27 updated some files
